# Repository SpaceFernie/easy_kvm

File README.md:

# Easy KVM
A small KVM project developped for myself. This will be a two-channel KVM, with one HDMI and three USB 2.0 buses.

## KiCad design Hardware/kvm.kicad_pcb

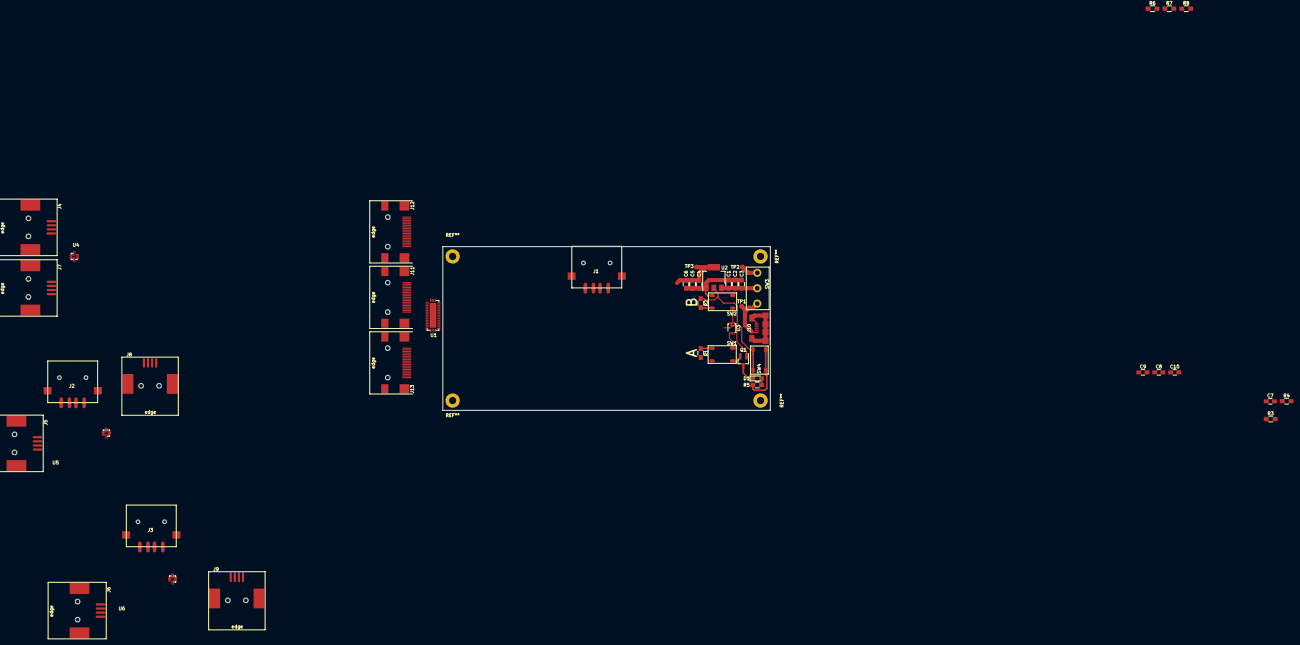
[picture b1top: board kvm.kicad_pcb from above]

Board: 2 copper layers, 100.0 x 50.0 mm, 46 parts (0 on the bottom side), 68 nets.

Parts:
C1, C6, C7, C8, C9, C10: 0.1uF; C_0805_HandSoldering
C2, C5: 1uF; C_0805_HandSoldering
C3: 4.7uF; C_0805_HandSoldering
C4: 10uF; C_0805_HandSoldering
D1: LED; LED_0805_HandSoldering
J1, J2, J3: USB_A; USB_A_SMD
J4, J5, J6, J7, J8, J9: USB_B; USB_B_SMD
J10: USB_B_Micro; micro_usb_smd
J11, J12, J13: HMDI; HDMI_SMD
Q1: Q_NMOS_GSD; SOT-23_Handsoldering
R1, R2: 1k; R_0805_HandSoldering
R3, R4: 10K; R_0805_HandSoldering
R5: 220; R_0805_HandSoldering
R6, R7: 2k; R_0805_HandSoldering
R8: 100k; R_0805_HandSoldering
SW1, SW2, SW4: SW_DIP_x01; TL3342F160_tact_switch
SW3: SW_DPDT_x2; GH39P0
TP1, TP2, TP3: Test_Point; 1.5mm_test_point
U1: TS3DV642; WQFN42
U2: SPX1117; SOT-223-3_TabPin2
U3: Double NAND; VSSOP8_2.4x2.1mm_Pitch0.5mm
U4, U5, U6: TS3USB3031; WQGN12

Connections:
+5V: C1.1, C2.1, C3.1, J11.18, J12.18, J13.18, R6.1, R7.1, SW3.2, U2.3
+5VA: J10.1, SW3.1, TP1.1
+5VD: J1.1, J2.1, J3.1, SW3.3, TP2.1
/HDMI/CEC: J11.13, U1.15
/HDMI/CECA: J12.13, U1.18
/HDMI/CECB: J13.13, U1.20
/HDMI/CLK+: J11.10, U1.12
/HDMI/CLK-: J11.12, U1.13
/HDMI/CLKA+: J12.10, U1.32
/HDMI/CLKA-: J12.12, U1.31
/HDMI/CLKB+: J13.10, U1.23
/HDMI/CLKB-: J13.12, U1.22
/HDMI/D0+: J11.7, U1.5
/HDMI/D0-: J11.9, U1.6
/HDMI/D0A+: J12.7, U1.38
/HDMI/D0A-: J12.9, U1.37
/HDMI/D0B+: J13.7, U1.29
/HDMI/D0B-: J13.9, U1.28
/HDMI/D1+: J11.4, U1.7
/HDMI/D1-: J11.6, U1.8
/HDMI/D1A+: J12.4, U1.36
/HDMI/D1A-: J12.6, U1.35
/HDMI/D1B+: J13.4, U1.27
/HDMI/D1B-: J13.6, U1.26
/HDMI/D2+: J11.1, U1.10
/HDMI/D2-: J11.3, U1.11
/HDMI/D2A+: J12.1, U1.34
/HDMI/D2A-: J12.3, U1.33
/HDMI/D2B+: J13.1, U1.25
/HDMI/D2B-: J13.3, U1.24
/HDMI/HPD: J11.19, R8.1, U1.14
/HDMI/HPDA: J12.19, U1.19
/HDMI/HPDB: J13.19, U1.21
/HDMI/SCL: J11.15, R7.2, U1.3
/HDMI/SCLA: J12.15, U1.42
/HDMI/SCLB: J13.15, U1.40
/HDMI/SDA: J11.16, R6.2, U1.4
/HDMI/SDAA: J12.16, U1.41
/HDMI/SDAB: J13.16, U1.39
/USB/USB1+: J1.3, U4.11
/USB/USB1-: J1.2, U4.10
/USB/USB1A+: J4.3, U4.3
/USB/USB1A-: J4.2, U4.4
/USB/USB1B+: J7.3, U4.5
/USB/USB1B-: J7.2, U4.6
/USB/USB2+: J2.3, U5.11
/USB/USB2-: J2.2, U5.10
/USB/USB2A+: J5.3, U5.3
/USB/USB2A-: J5.2, U5.4
/USB/USB2B+: J8.3, U5.5
/USB/USB2B-: J8.2, U5.6
/USB/USB3+: J3.3, U6.11
/USB/USB3-: J3.2, U6.10
/USB/USB3A+: J6.3, U6.3
/USB/USB3A-: J6.2, U6.4
/USB/USB3B+: J9.3, U6.5
/USB/USB3B-: J9.2, U6.6
CTRL: Q1.1, U1.17, U3.5, U3.7, U4.1, U5.1, U6.1
GND: C1.2, C2.2, C3.2, C4.2, C5.2, C6.2, C7.2, C8.2, C9.2, C10.2, J1.4, J1.5, J2.4, J2.5, J3.4, J3.5, J4.4, J4.5, J5.4, J5.5, J6.4, J6.5, J7.4, J7.5, J8.4, J8.5, J9.4, J9.5, J10.5, J10.6, J11.2, J11.5, J11.8, J11.17, J12.2, J12.5, J12.8, J12.17, J13.2, J13.5, J13.8, J13.17, Q1.2, R8.2, SW1.2, SW2.2, U1.43, U2.1, U3.4, U4.2, U4.9, U5.2, U5.9, U6.2, U6.9
unnamed: D1.1, Q1.3
unnamed: D1.2, R5.2
unnamed: R1.1, SW1.1, U3.1
unnamed: R2.2, SW2.1, U3.6
unnamed: R3.1, U1.2
unnamed: R4.1, U1.16
unnamed: R5.1, SW4.2
unnamed: U3.2, U3.3
VCC: C4.1, C5.1, C6.1, C7.1, C8.1, C9.1, C10.1, R1.2, R2.1, R3.2, R4.2, SW4.1, TP3.1, U1.1, U2.2, U3.8, U4.12, U5.12, U6.12

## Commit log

2017-12-29 Added hardware files and created software and documentation directories
2017-12-29 Added power stage, control logic, and USB muxes
2018-01-01 Designed layout for power stage and for control logic
2018-01-02 USB ports and USB muxes to change
